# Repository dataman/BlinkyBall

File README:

Work that I've been doing on BlinkBall,
No, not Charley's Blinky Balls,
But Blinky Ball.
A motion activated circuit,
Based on the Tiny Cylon Code,
An not more than 15mm square!

I started this back in January 2012.
Finally figuring out what I did wrong.
Hope to be done by October 2012.

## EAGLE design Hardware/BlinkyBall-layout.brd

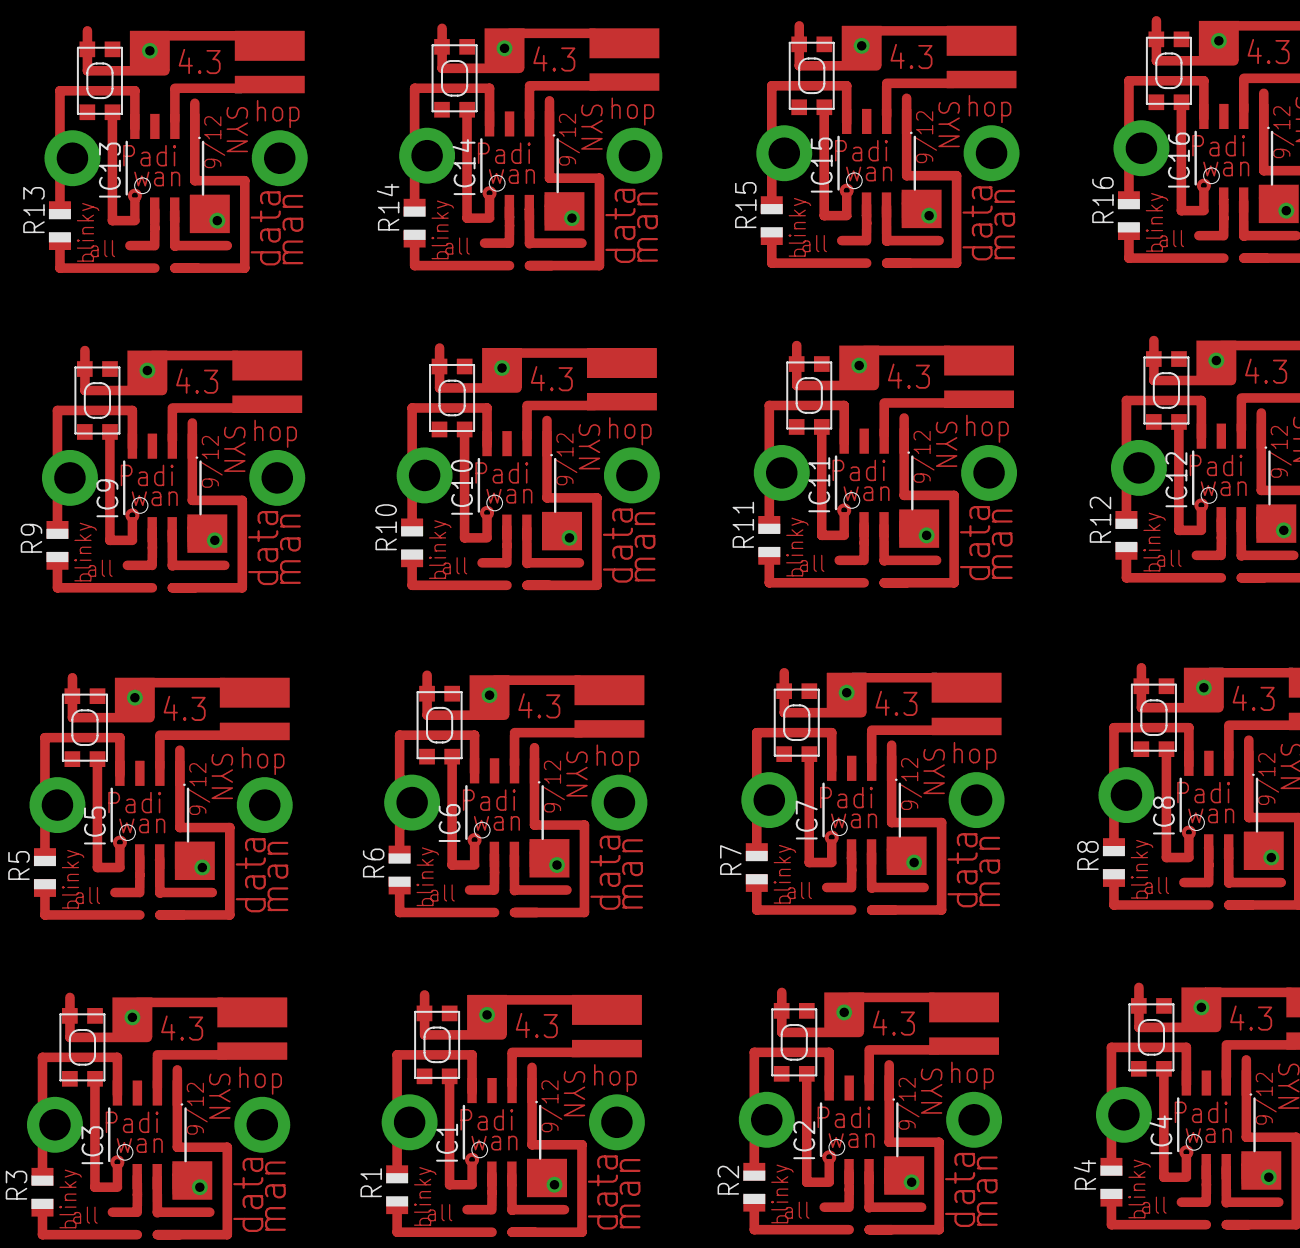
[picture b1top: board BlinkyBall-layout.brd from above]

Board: 2 copper layers, 48 parts (0 on the bottom side), 16 nets.

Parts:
E$1, E$2, E$3, E$4, E$5, E$6, E$7, E$8, E$9, E$10, E$11, E$12, E$13, E$14, E$15, E$16: KMR2
IC1, IC2, IC3, IC4, IC5, IC6, IC7, IC8, IC9, IC10, IC11, IC12, IC13, IC14, IC15, IC16: TINY13-20SSU; 8S1
R1, R2, R3, R4, R5, R6, R7, R8, R9, R10, R11, R12, R13, R14, R15, R16: R0805

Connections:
unnamed: IC1.4, R1.2
unnamed: IC2.4, R2.2
unnamed: IC4.4, R4.2
unnamed: IC5.4, R5.2
unnamed: IC3.4, R3.2
unnamed: IC6.4, R6.2
unnamed: IC7.4, R7.2
unnamed: IC8.4, R8.2
unnamed: IC9.4, R9.2
unnamed: IC10.4, R10.2
unnamed: IC11.4, R11.2
unnamed: IC12.4, R12.2
unnamed: IC13.4, R13.2
unnamed: IC14.4, R14.2
unnamed: IC15.4, R15.2
unnamed: IC16.4, R16.2

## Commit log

2012-09-14 Fixups to board
2012-09-15 well, it compiles?
2012-09-16 Revisions to board
    Duh, I had used int1 rather than int0. No wonder tilt switch did not
    work. I guess you need to get away from a project to see it clearly
2012-09-16 tinkering
2012-09-18 working on code
2012-09-19 working through it
2012-09-19 remove v from board.
2012-09-19 Staging BlinkBall.C for diff changes
2012-09-19 Should work
2012-09-19 Change hardcoded value to MAXTILT
    Number of times to blink after tilt event.
2012-09-20 Added multiple layout board
2012-09-20 working it
2012-09-22 Adjust for LED
2012-09-22 Woot Woot! I think Test09 is a keeper!
    I've got it working!
    Test09 seems to be gold.
2012-09-22 Cleaning up
2012-09-22 cleanup part II
2012-09-22 Adjusting Layout, v4.2
2012-09-23 Final Board Adjustments?
2012-10-01 Firmware v6
